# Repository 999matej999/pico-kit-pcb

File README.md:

# Pico Kit PCB #

## Files
* [Schematic](./rpi_pico_kit/RPi-Pico-Kit.pdf)
* [Gerber](./rpi_pico_kit/gerbers/)

## 3D Model

## Layout

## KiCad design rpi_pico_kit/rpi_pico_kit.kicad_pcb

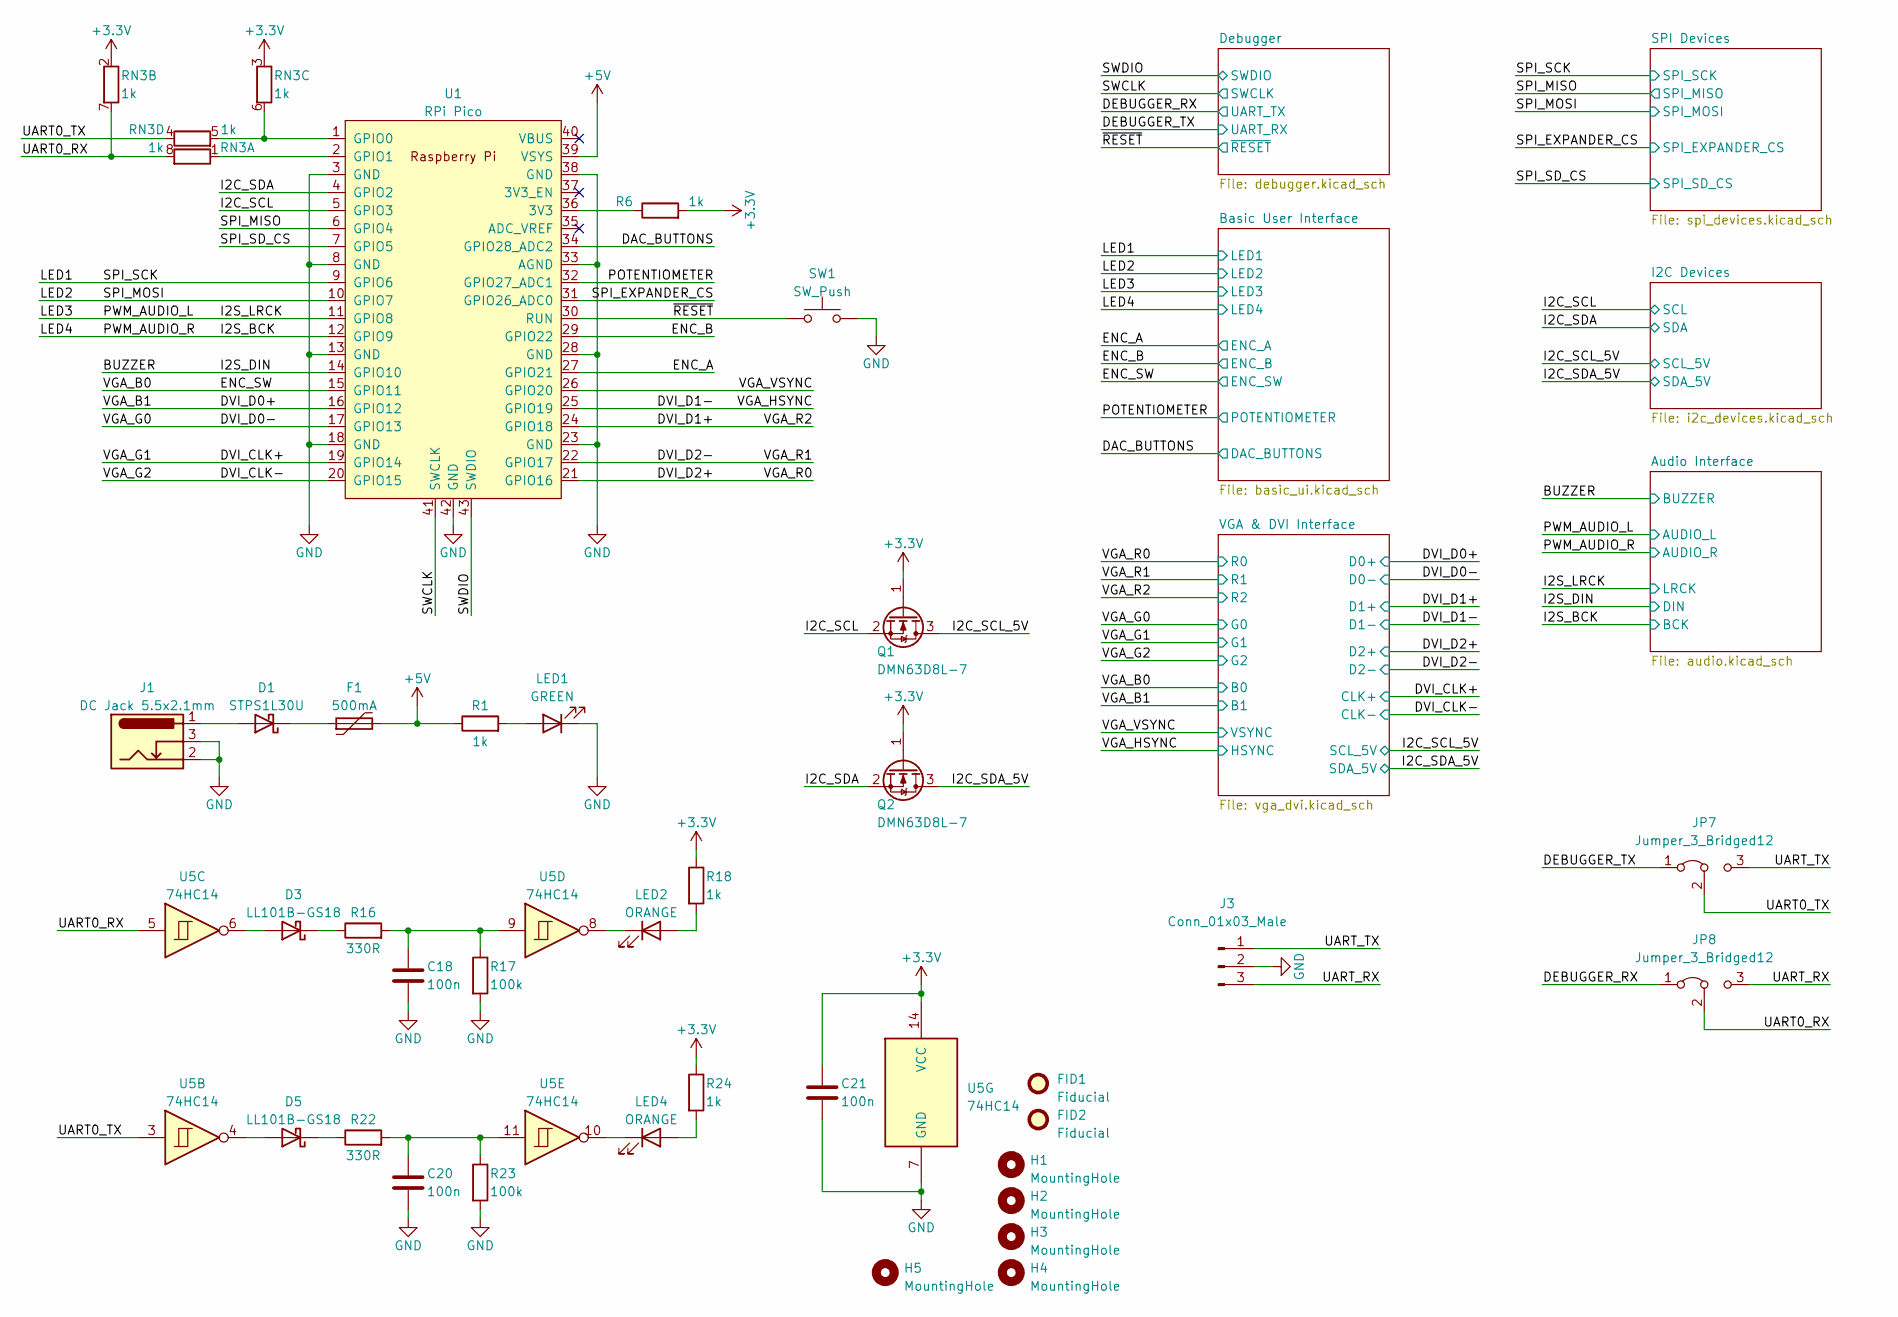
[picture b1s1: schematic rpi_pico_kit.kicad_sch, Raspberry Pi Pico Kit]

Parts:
C18, C20, C21: 100n; C_0603_1608Metric_Pad1.08x0.95mm_HandSolder; Manufacturer Part Number C0805C104M3RAC7800
D1: STPS1L30U; D_SMB; Manufacturer Part Number STPS1L30U
D3, D5: LL101B-GS18; D_MiniMELF; Manufacturer Part Number LL101B-GS18
F1: 500mA; Fuse_1206_3216Metric_Pad1.42x1.75mm_HandSolder; Manufacturer Part Number 0ZCJ0050FF2G
FID1, FID2: Fiducial; Fiducial_0.75mm_Mask1.5mm
H1, H2, H3, H4, H5: MountingHole; MountingHole_2.7mm_M2.5
J1: DC Jack 5.5x2.1mm; BarrelJack_GCT_DCJ200-10-A_Horizontal; Manufacturer Part Number 54-00129
J3: Conn_01x03_Male; PinHeader_1x03_P2.54mm_Vertical; Manufacturer Part Number PinHeader_1x03
JP7, JP8: Jumper_3_Bridged12; JumperTHT_3_P2.54mm_Bridged12; Manufacturer Part Number PinHeader_1x03
LED1: GREEN; LED_0805_2012Metric_Pad1.15x1.40mm_HandSolder; Manufacturer Part Number 150080VS75000
LED2, LED4: ORANGE; LED_0805_2012Metric_Pad1.15x1.40mm_HandSolder; Manufacturer Part Number LTST-C170KFKT
Q1, Q2: DMN63D8L-7; SOT-23; Manufacturer Part Number DMN63D8L-7
R1, R6, R18, R24: 1k; R_0603_1608Metric_Pad0.98x0.95mm_HandSolder; Manufacturer Part Number RC0805FR-071KL
R16, R22: 330R; R_0603_1608Metric_Pad0.98x0.95mm_HandSolder; Manufacturer Part Number RC0805FR-13330RL
R17, R23: 100k; R_0603_1608Metric_Pad0.98x0.95mm_HandSolder; Manufacturer Part Number RC0805FR-07100KL
RN3: 1k; R_Array_Convex_4x0603
SW1: SW_Push; SW_SPST_Omron_B3FS-100xP_12; Manufacturer Part Number TD-03XAT-A00-TR
U1: RPi Pico; RPi_Pico_THT_socket; Manufacturer Part Number SC0915
U5: 74HC14; SOIC-14_3.9x8.7mm_P1.27mm; Manufacturer Part Number 74HC14S14-13

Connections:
+3V3: C21.2, Q1.1 (G), Q2.1 (G), R6.2, R18.1, R24.1, RN3.2 (R2.1), RN3.3 (R3.1), U5.14 (VCC); also elsewhere on the board
+5V: F1.2, R1.1, U1.39 (VSYS); also elsewhere on the board
/BUZZER: U1.14 (GPIO10); also elsewhere on the board
/DAC_BUTTONS: U1.34 (GPIO28_ADC2); also elsewhere on the board
/DEBUGGER_RX: JP8.1 (A); also elsewhere on the board
/DEBUGGER_TX: JP7.1 (A); also elsewhere on the board
/DVI_CLK+: U1.19 (GPIO14); also elsewhere on the board
/DVI_CLK-: U1.20 (GPIO15); also elsewhere on the board
/DVI_D0+: U1.16 (GPIO12); also elsewhere on the board
/DVI_D0-: U1.17 (GPIO13); also elsewhere on the board
/DVI_D1+: U1.24 (GPIO18); also elsewhere on the board
/DVI_D1-: U1.25 (GPIO19); also elsewhere on the board
/DVI_D2+: U1.21 (GPIO16); also elsewhere on the board
/DVI_D2-: U1.22 (GPIO17); also elsewhere on the board
/ENC_A: U1.27 (GPIO21); also elsewhere on the board
/ENC_B: U1.29 (GPIO22); also elsewhere on the board
/ENC_SW: U1.15 (GPIO11); also elsewhere on the board
/I2C_SCL: Q1.2 (S), U1.5 (GPIO3); also elsewhere on the board
/I2C_SCL_5V: Q1.3 (D); also elsewhere on the board
/I2C_SDA: Q2.2 (S), U1.4 (GPIO2); also elsewhere on the board
/I2C_SDA_5V: Q2.3 (D); also elsewhere on the board
/I2S_BCK: U1.12 (GPIO9); also elsewhere on the board
/I2S_LRCK: U1.11 (GPIO8); also elsewhere on the board
/LED1: U1.9 (GPIO6); also elsewhere on the board
/LED2: U1.10 (GPIO7); also elsewhere on the board
/POTENTIOMETER: U1.32 (GPIO27_ADC1); also elsewhere on the board
/SPI_EXPANDER_CS: U1.31 (GPIO26_ADC0); also elsewhere on the board
/SPI_MISO: U1.6 (GPIO4); also elsewhere on the board
/SPI_SD_CS: U1.7 (GPIO5); also elsewhere on the board
/SWCLK: U1.41 (SWCLK); also elsewhere on the board
/SWDIO: U1.43 (SWDIO); also elsewhere on the board
/UART0_RX: JP8.2 (C), RN3.7 (R2.2), RN3.8 (R1.2), U5.5
/UART0_TX: JP7.2 (C), RN3.4 (R4.1), U5.3
/UART_RX: J3.3, JP8.3 (B)
/UART_TX: J3.1, JP7.3 (B)
/VGA_VSYNC: U1.26 (GPIO20); also elsewhere on the board
/~RESET: SW1.1, U1.30 (RUN); also elsewhere on the board
GND: C18.1, C20.1, C21.1, J1.2, J1.3, J3.2, LED1.1 (K), R17.2, R23.2, SW1.2, U1.3 (GND), U1.8 (GND), U1.13 (GND), U1.18 (GND), U1.23 (GND), U1.28 (GND), U1.33 (AGND), U1.38 (GND), U1.42 (GND), U5.7 (GND); also elsewhere on the board
unnamed: C18.2, R16.2, R17.1, U5.9
unnamed: C20.2, R22.2, R23.1, U5.11
unnamed: D1.2 (A), J1.1
unnamed: D1.1 (K), F1.1
unnamed: D3.2 (A), U5.6
unnamed: D3.1 (K), R16.1
unnamed: D5.2 (A), U5.4
unnamed: D5.1 (K), R22.1
unnamed: LED1.2 (A), R1.2
unnamed: LED2.2 (A), R18.2
unnamed: LED2.1 (K), U5.8
unnamed: LED4.2 (A), R24.2
unnamed: LED4.1 (K), U5.10
unnamed: RN3.1 (R1.1), U1.2 (GPIO1)
unnamed: RN3.5 (R4.2), RN3.6 (R3.2), U1.1 (GPIO0)
unnamed: R6.1, U1.36 (3V3)

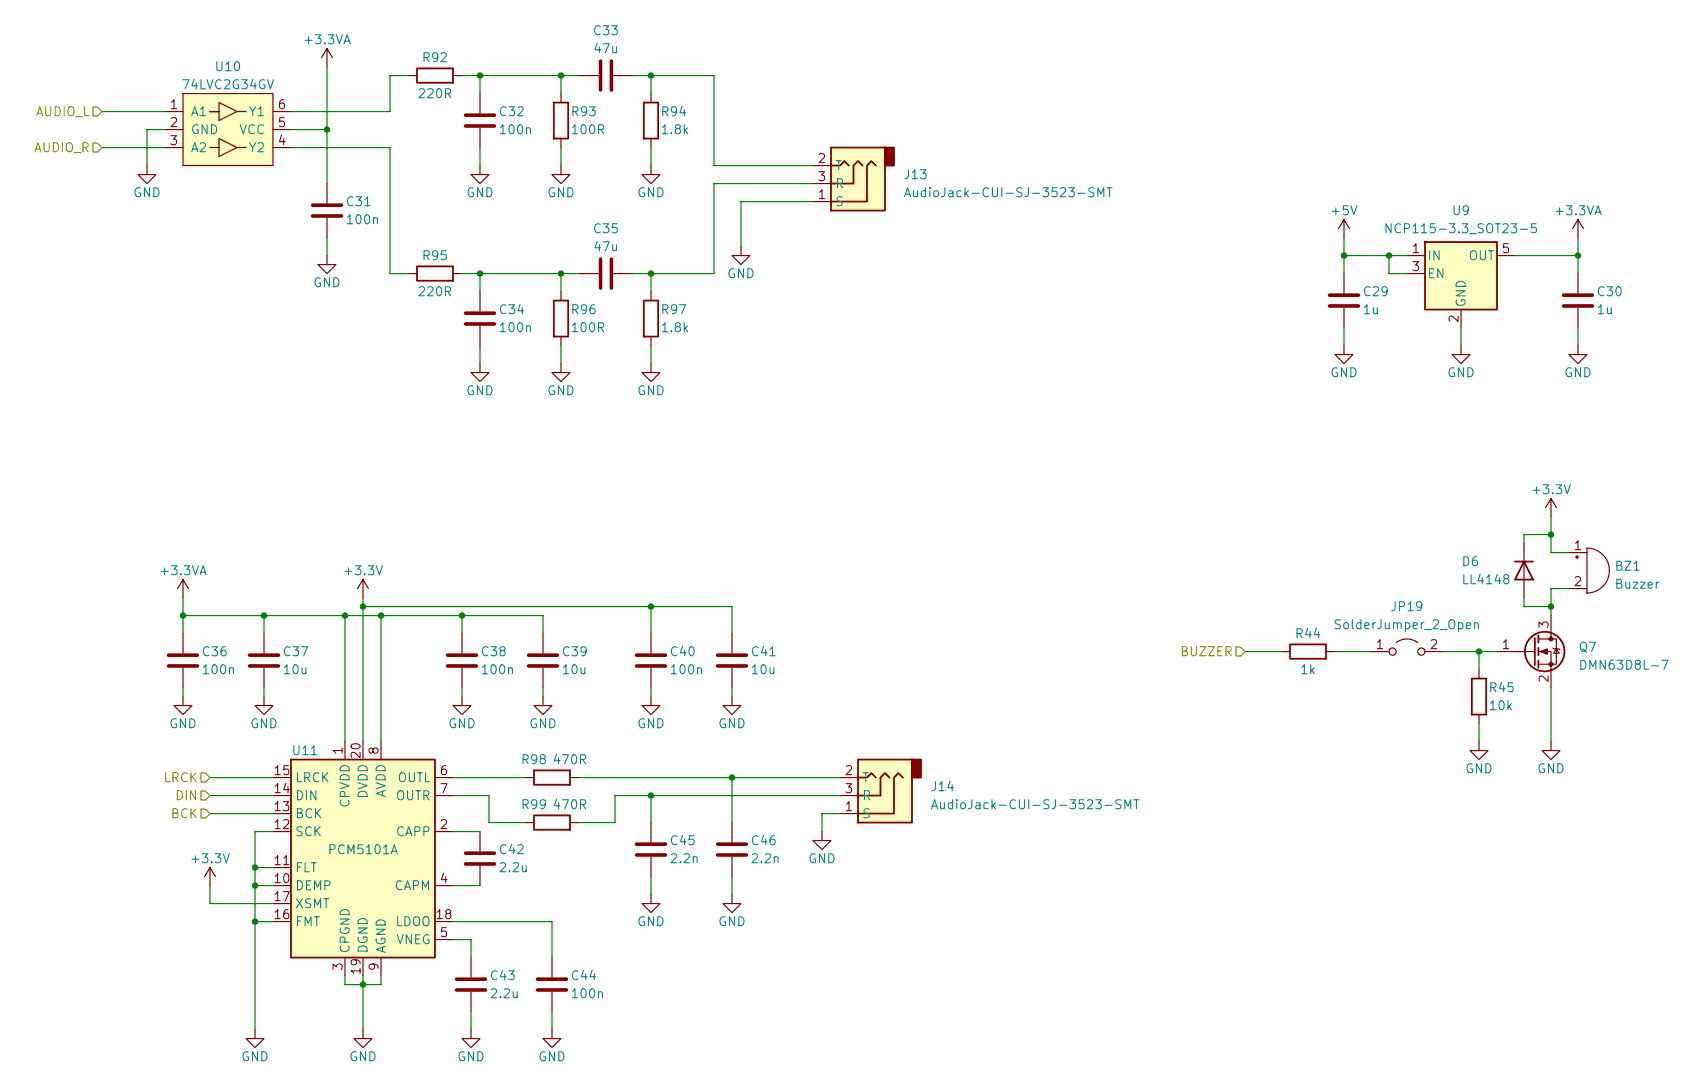
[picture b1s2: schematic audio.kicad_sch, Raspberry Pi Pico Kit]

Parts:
BZ1: Buzzer; Buzzer_12x9.5RM7.6; Manufacturer Part Number LA216001
C29, C30: 1u; C_0805_2012Metric_Pad1.18x1.45mm_HandSolder; Manufacturer Part Number C0805C105Z4VAC7800
C31, C32, C34, C36, C38, C40, C44: 100n; C_0603_1608Metric_Pad1.08x0.95mm_HandSolder; Manufacturer Part Number C0805C104M3RAC7800
C33, C35: 47u; C_0805_2012Metric_Pad1.18x1.45mm_HandSolder; Manufacturer Part Number CL21A476MRYNNNE
C37, C39, C41: 10u; C_0805_2012Metric_Pad1.18x1.45mm_HandSolder; Manufacturer Part Number CL21A106KOQNNNG
C42, C43: 2.2u; C_0805_2012Metric_Pad1.18x1.45mm_HandSolder; Manufacturer Part Number C0805C225Z4VAC7800
C45, C46: 2.2n; C_0603_1608Metric_Pad1.08x0.95mm_HandSolder; Manufacturer Part Number C0805C222K5RAC7800
D6: LL4148; D_MiniMELF; Manufacturer Part Number LL4148
J13, J14: AudioJack-CUI-SJ-3523-SMT; CUI_SJ-3523-audio-jack; Manufacturer Part Number SJ-3523-SMT-TR
JP19: SolderJumper_2_Open; JumperTHT_2_P2.54mm_Open; Manufacturer Part Number PinHeader_1x02
Q7: DMN63D8L-7; SOT-23; Manufacturer Part Number DMN63D8L-7
R44: 1k; R_0603_1608Metric_Pad0.98x0.95mm_HandSolder; Manufacturer Part Number RC0805FR-071KL
R45: 10k; R_0603_1608Metric_Pad0.98x0.95mm_HandSolder; Manufacturer Part Number RC0805FR-0710KL
R92, R95: 220R; R_0603_1608Metric_Pad0.98x0.95mm_HandSolder; Manufacturer Part Number RC0805FR-07220RL
R93, R96: 100R; R_0603_1608Metric_Pad0.98x0.95mm_HandSolder; Manufacturer Part Number RC0805FR-07100RL
R94, R97: 1.8k; R_0603_1608Metric_Pad0.98x0.95mm_HandSolder; Manufacturer Part Number RC0805FR-071K8L
R98, R99: 470R; R_0603_1608Metric_Pad0.98x0.95mm_HandSolder; Manufacturer Part Number RC0805FR-07470RL
U9: NCP115-3.3_SOT23-5; SOT-23-5; Manufacturer Part Number NCP115ASN330T2G
U10: 74LVC2G34GV; SC-74-6_1.5x2.9mm_P0.95mm; Manufacturer Part Number 74LVC2G34GV,125
U11: PCM5101A; TSSOP-20_4.4x6.5mm_P0.65mm

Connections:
+3.3VA: C30.2, C31.2, C36.2, C37.2, C38.2, C39.2, U9.5 (OUT), U10.5 (VCC), U11.1 (CPVDD), U11.8 (AVDD)
+3V3: BZ1.1 (-), C40.2, C41.2, D6.1 (K), U11.17 (XSMT), U11.20 (DVDD); also elsewhere on the board
+5V: C29.2, U9.1 (IN), U9.3 (EN); also elsewhere on the board
/BUZZER: R44.1, U11.14 (DIN); also elsewhere on the board
/I2S_BCK: U10.3 (A2), U11.13 (BCK); also elsewhere on the board
/I2S_LRCK: U10.1 (A1), U11.15 (LRCK); also elsewhere on the board
GND: C29.1, C30.1, C31.1, C32.1, C34.1, C36.1, C37.1, C38.1, C39.1, C40.1, C41.1, C43.1, C44.1, C45.1, C46.1, J13.1 (S), J14.1 (S), Q7.2 (S), R45.2, R93.2, R94.2, R96.2, R97.2, U9.2 (GND), U10.2 (GND), U11.3 (CPGND), U11.9 (AGND), U11.10 (DEMP), U11.11 (FLT), U11.12 (SCK), U11.16 (FMT), U11.19 (DGND); also elsewhere on the board
unnamed: BZ1.2 (+), D6.2 (A), Q7.3 (D)
unnamed: C32.2, C33.1, R92.2, R93.1
unnamed: C34.2, C35.1, R95.2, R96.1
unnamed: C35.2, J13.3 (R), R97.1
unnamed: C33.2, J13.2 (T), R94.1
unnamed: C45.2, J14.3 (R), R99.2
unnamed: C46.2, J14.2 (T), R98.2
unnamed: JP19.1 (A), R44.2
unnamed: JP19.2 (B), Q7.1 (G), R45.1
unnamed: R92.1, U10.6 (Y1)
unnamed: R95.1, U10.4 (Y2)
unnamed: C42.1, U11.4 (CAPM)
unnamed: C42.2, U11.2 (CAPP)
unnamed: C44.2, U11.18 (LDOO)
unnamed: R98.1, U11.6 (OUTL)
unnamed: R99.1, U11.7 (OUTR)
unnamed: C43.2, U11.5 (VNEG)

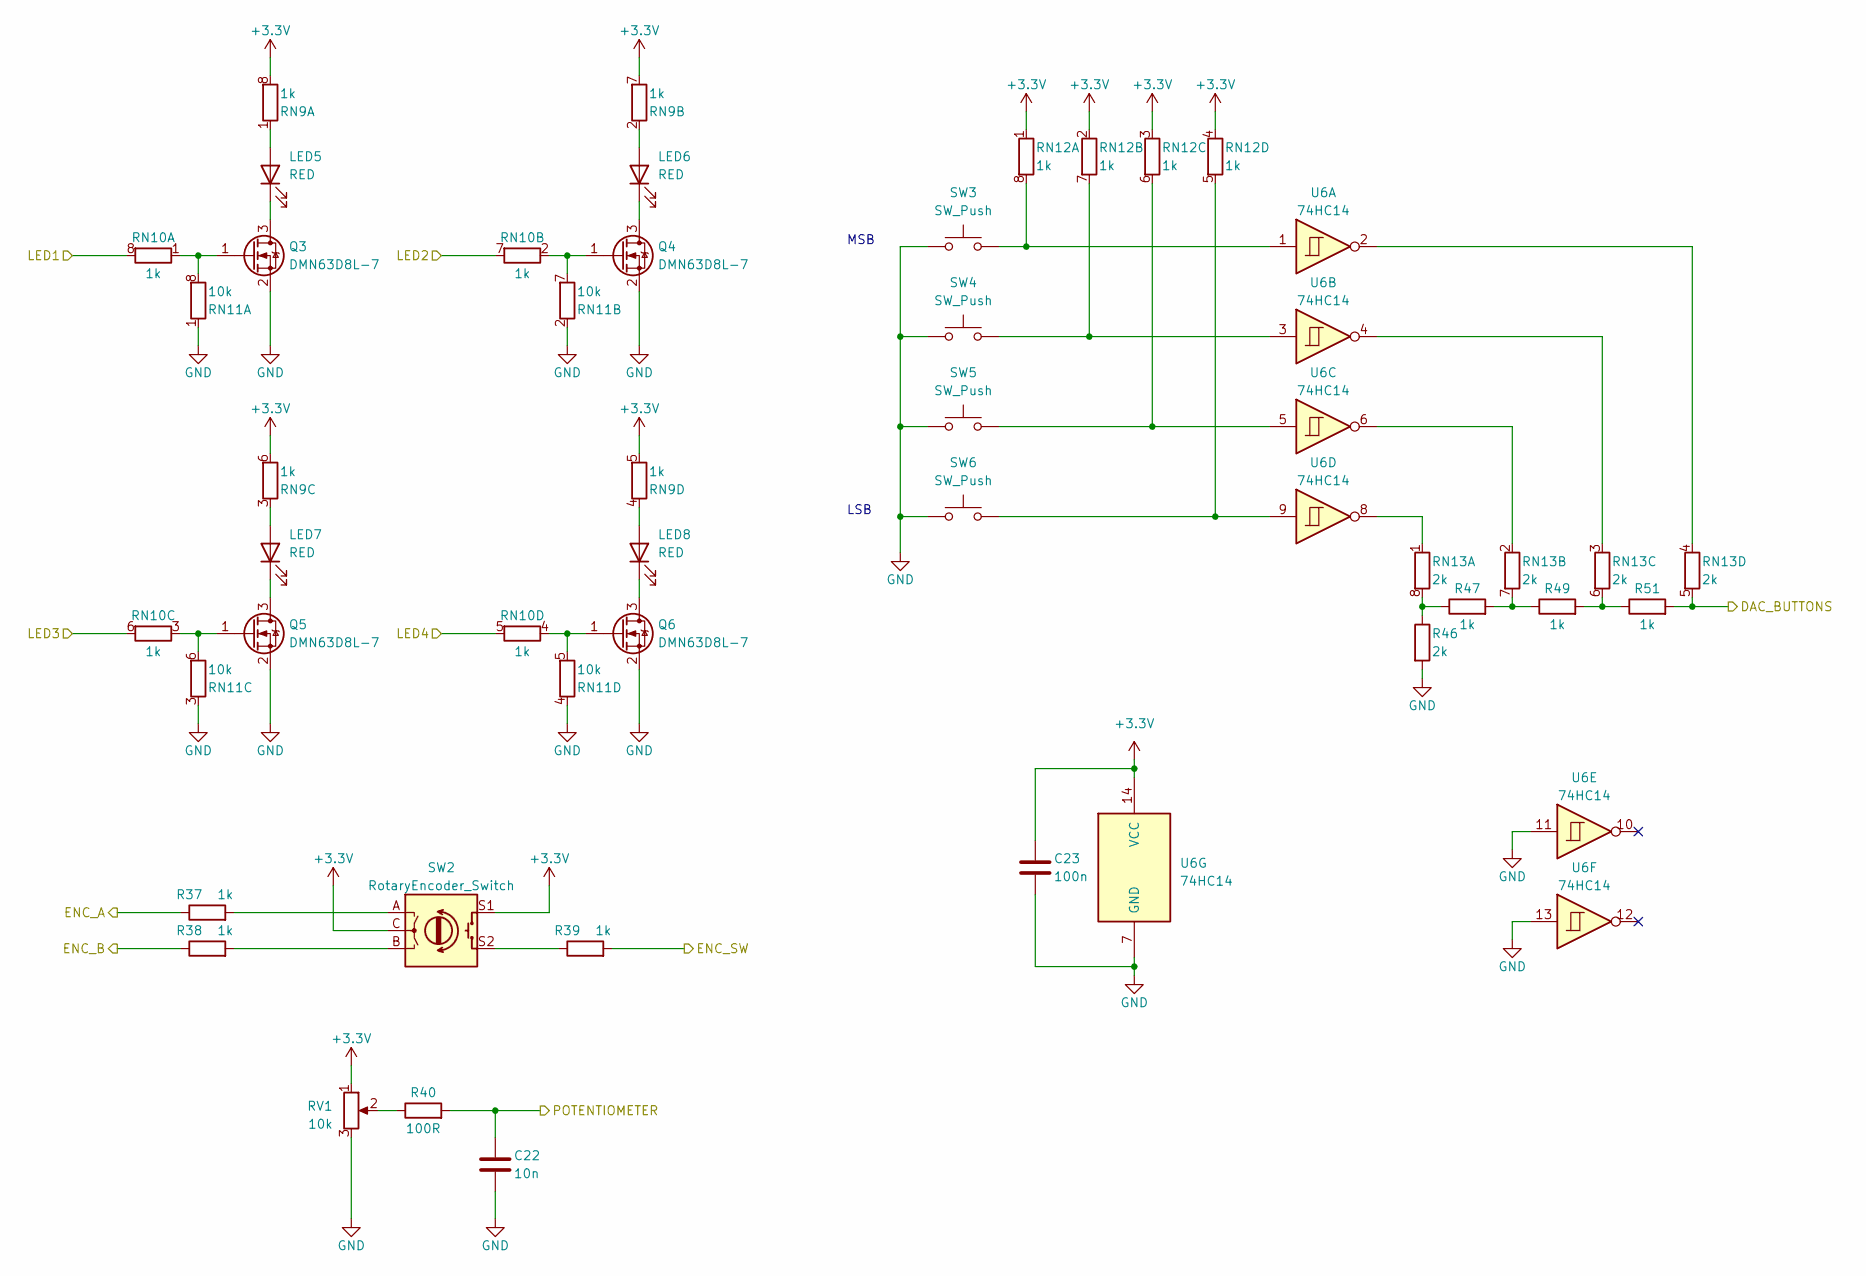
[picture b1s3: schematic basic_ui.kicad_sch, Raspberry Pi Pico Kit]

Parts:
C22: 10n; C_0603_1608Metric_Pad1.08x0.95mm_HandSolder; Manufacturer Part Number C0805C103K5RAC7210
C23: 100n; C_0603_1608Metric_Pad1.08x0.95mm_HandSolder; Manufacturer Part Number C0805C104M3RAC7800
LED5, LED6, LED7, LED8: RED; LED_0805_2012Metric_Pad1.15x1.40mm_HandSolder; Manufacturer Part Number 150080SS75000
Q3, Q4, Q5, Q6: DMN63D8L-7; SOT-23; Manufacturer Part Number DMN63D8L-7
R37, R38, R39, R47, R49, R51: 1k; R_0603_1608Metric_Pad0.98x0.95mm_HandSolder; Manufacturer Part Number RC0805FR-071KL
R40: 100R; R_0603_1608Metric_Pad0.98x0.95mm_HandSolder; Manufacturer Part Number RC0805FR-07100RL
R46: 2k; R_0603_1608Metric_Pad0.98x0.95mm_HandSolder; Manufacturer Part Number RC0805FR-072KL
RN9, RN10, RN12: 1k; R_Array_Convex_4x0603
RN11: 10k; R_Array_Convex_4x0603
RN13: 2k; R_Array_Convex_4x0603
RV1: 10k; Potentiometer_Bourns_PTV09A-1_Single_Vertical; Manufacturer Part Number PT01-B125D-B103
SW2: RotaryEncoder_Switch; RotaryEncoder_Alps_EC11E-Switch_Vertical_H20mm; Manufacturer Part Number EN11-HSM1BF20
SW3, SW4, SW5, SW6: SW_Push; SW_SPST_Omron_B3FS-100xP_12; Manufacturer Part Number TD-03XAT-A00-TR
U6: 74HC14; SOIC-14_3.9x8.7mm_P1.27mm; Manufacturer Part Number 74HC14S14-13

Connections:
+3V3: C23.2, RN9.5 (R4.2), RN9.6 (R3.2), RN9.7 (R2.2), RN9.8 (R1.2), RN12.1 (R1.1), RN12.2 (R2.1), RN12.3 (R3.1), RN12.4 (R4.1), RV1.1, SW2.C, SW2.S1, U6.14 (VCC); also elsewhere on the board
/DAC_BUTTONS: R51.2, RN13.5 (R4.2); also elsewhere on the board
/ENC_A: R37.1; also elsewhere on the board
/ENC_B: R38.1; also elsewhere on the board
/ENC_SW: R39.2; also elsewhere on the board
/I2S_BCK: RN10.5 (R4.2); also elsewhere on the board
/I2S_LRCK: RN10.6 (R3.2); also elsewhere on the board
/LED1: RN10.8 (R1.2); also elsewhere on the board
/LED2: RN10.7 (R2.2); also elsewhere on the board
/POTENTIOMETER: C22.1, R40.2; also elsewhere on the board
GND: C22.2, C23.1, Q3.2 (S), Q4.2 (S), Q5.2 (S), Q6.2 (S), R46.2, RN11.1 (R1.1), RN11.2 (R2.1), RN11.3 (R3.1), RN11.4 (R4.1), RV1.3, SW3.2, SW4.2, SW5.2, SW6.2, U6.7 (GND), U6.11, U6.13; also elsewhere on the board
unnamed: LED5.2 (A), RN9.1 (R1.1)
unnamed: LED5.1 (K), Q3.3 (D)
unnamed: LED6.2 (A), RN9.2 (R2.1)
unnamed: LED6.1 (K), Q4.3 (D)
unnamed: LED7.2 (A), RN9.3 (R3.1)
unnamed: LED7.1 (K), Q5.3 (D)
unnamed: LED8.2 (A), RN9.4 (R4.1)
unnamed: LED8.1 (K), Q6.3 (D)
unnamed: Q3.1 (G), RN10.1 (R1.1), RN11.8 (R1.2)
unnamed: Q4.1 (G), RN10.2 (R2.1), RN11.7 (R2.2)
unnamed: Q5.1 (G), RN10.3 (R3.1), RN11.6 (R3.2)
unnamed: Q6.1 (G), RN10.4 (R4.1), RN11.5 (R4.2)
unnamed: R37.2, SW2.A
unnamed: R38.2, SW2.B
unnamed: R39.1, SW2.S2
unnamed: R40.1, RV1.2
unnamed: RN12.8 (R1.2), SW3.1, U6.1
unnamed: RN12.7 (R2.2), SW4.1, U6.3
unnamed: RN12.6 (R3.2), SW5.1, U6.5
unnamed: RN12.5 (R4.2), SW6.1, U6.9
unnamed: RN13.1 (R1.1), U6.8
unnamed: R46.1, R47.1, RN13.8 (R1.2)
unnamed: RN13.2 (R2.1), U6.6
unnamed: R47.2, R49.1, RN13.7 (R2.2)
unnamed: RN13.3 (R3.1), U6.4
unnamed: R49.2, R51.1, RN13.6 (R3.2)
unnamed: RN13.4 (R4.1), U6.2

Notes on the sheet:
LSB
MSB

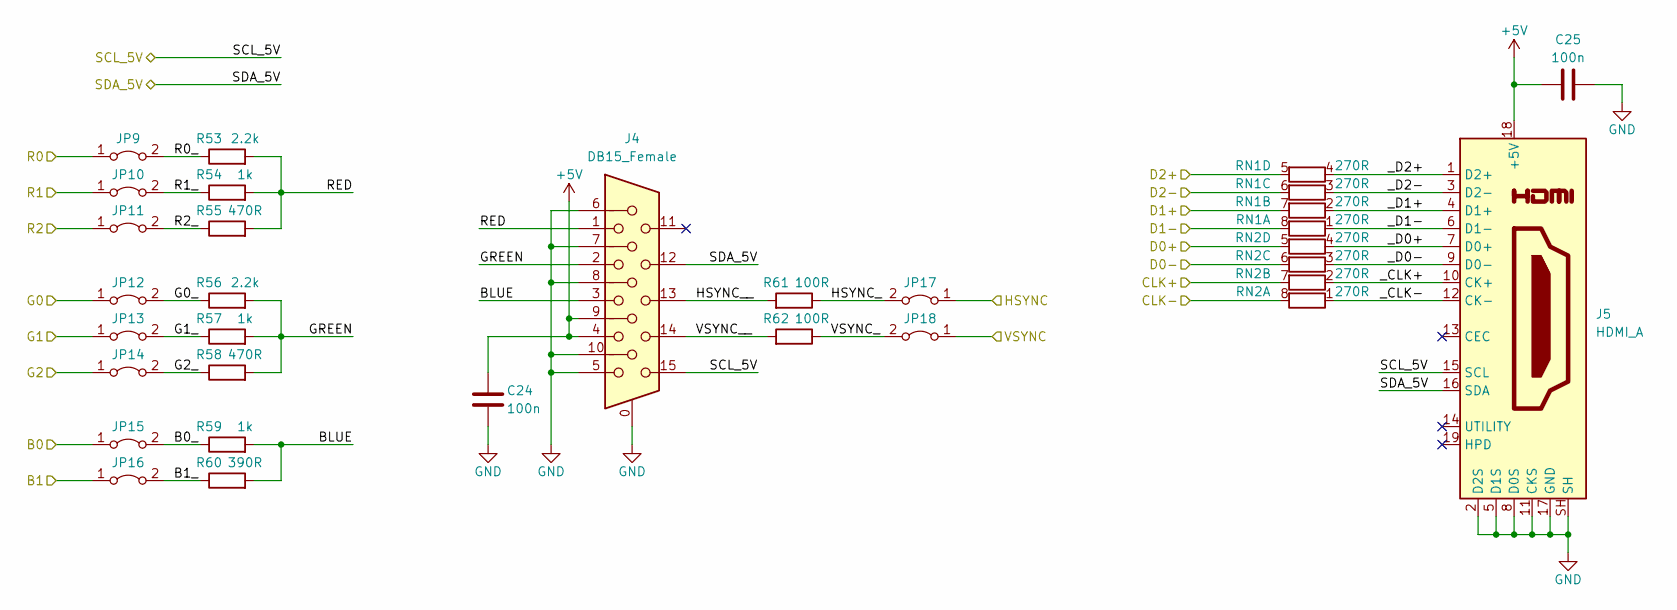
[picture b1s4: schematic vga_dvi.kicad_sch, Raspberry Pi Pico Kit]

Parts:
C24, C25: 100n; C_0603_1608Metric_Pad1.08x0.95mm_HandSolder; Manufacturer Part Number C0805C104M3RAC7800
J4: DB15_Female; DSUB-15-HD_Female_Horizontal_P2.29x1.98mm_EdgePinOffset3.03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
J5: HDMI_A; STEWART_SS-53000-001; Manufacturer Part Number SS-53000-001
JP9, JP10, JP11, JP12, JP13, JP14, JP15, JP16, JP17, JP18: Jumper_2_Bridged; JumperTHT_2_P2.54mm_Bridged; Manufacturer Part Number PinHeader_1x02
R53, R56: 2.2k; R_0603_1608Metric_Pad0.98x0.95mm_HandSolder; Manufacturer Part Number RC0805FR-072K2L
R54, R57, R59: 1k; R_0603_1608Metric_Pad0.98x0.95mm_HandSolder; Manufacturer Part Number RC0805FR-071KL
R55, R58: 470R; R_0603_1608Metric_Pad0.98x0.95mm_HandSolder; Manufacturer Part Number RC0805FR-07470RL
R60: 390R; R_0603_1608Metric_Pad0.98x0.95mm_HandSolder; Manufacturer Part Number RC0805FR-07390RL
R61, R62: 100R; R_0603_1608Metric_Pad0.98x0.95mm_HandSolder; Manufacturer Part Number RC0805FR-07100RL
RN1, RN2: 270R; R_Array_Convex_4x0603

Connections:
+5V: C24.2, C25.1, J4.4, J4.9, J5.18 (+5V); also elsewhere on the board
/DVI_CLK+: JP13.1 (A), RN2.7 (R2.2); also elsewhere on the board
/DVI_CLK-: JP14.1 (A), RN2.8 (R1.2); also elsewhere on the board
/DVI_D0+: JP16.1 (A), RN2.5 (R4.2); also elsewhere on the board
/DVI_D0-: JP12.1 (A), RN2.6 (R3.2); also elsewhere on the board
/DVI_D1+: JP11.1 (A), RN1.7 (R2.2); also elsewhere on the board
/DVI_D1-: JP17.1 (A), RN1.8 (R1.2); also elsewhere on the board
/DVI_D2+: JP9.1 (A), RN1.5 (R4.2); also elsewhere on the board
/DVI_D2-: JP10.1 (A), RN1.6 (R3.2); also elsewhere on the board
/ENC_SW: JP15.1 (A); also elsewhere on the board
/I2C_SCL_5V: J4.15, J5.15 (SCL); also elsewhere on the board
/I2C_SDA_5V: J4.12, J5.16 (SDA); also elsewhere on the board
/VGA & DVI Interface/B0_: JP15.2 (B), R59.1
/VGA & DVI Interface/B1_: JP16.2 (B), R60.1
/VGA & DVI Interface/BLUE: J4.3, R59.2, R60.2
/VGA & DVI Interface/G0_: JP12.2 (B), R56.1
/VGA & DVI Interface/G1_: JP13.2 (B), R57.1
/VGA & DVI Interface/G2_: JP14.2 (B), R58.1
/VGA & DVI Interface/GREEN: J4.2, R56.2, R57.2, R58.2
/VGA & DVI Interface/HSYNC_: JP17.2 (B), R61.1
/VGA & DVI Interface/HSYNC__: J4.13, R61.2
/VGA & DVI Interface/R0_: JP9.2 (B), R53.1
/VGA & DVI Interface/R1_: JP10.2 (B), R54.1
/VGA & DVI Interface/R2_: JP11.2 (B), R55.1
/VGA & DVI Interface/RED: J4.1, R53.2, R54.2, R55.2
/VGA & DVI Interface/VSYNC_: JP18.2 (B), R62.1
/VGA & DVI Interface/VSYNC__: J4.14, R62.2
/VGA & DVI Interface/_CLK+: J5.10 (CK+), RN2.2 (R2.1)
/VGA & DVI Interface/_CLK-: J5.12 (CK-), RN2.1 (R1.1)
/VGA & DVI Interface/_D0+: J5.7 (D0+), RN2.4 (R4.1)
/VGA & DVI Interface/_D0-: J5.9 (D0-), RN2.3 (R3.1)
/VGA & DVI Interface/_D1+: J5.4 (D1+), RN1.2 (R2.1)
/VGA & DVI Interface/_D1-: J5.6 (D1-), RN1.1 (R1.1)
/VGA & DVI Interface/_D2+: J5.1 (D2+), RN1.4 (R4.1)
/VGA & DVI Interface/_D2-: J5.3 (D2-), RN1.3 (R3.1)
/VGA_VSYNC: JP18.1 (A); also elsewhere on the board
GND: C24.1, C25.2, J4.0, J4.5, J4.6, J4.7, J4.8, J4.10, J5.2 (D2S), J5.5 (D1S), J5.8 (D0S), J5.11 (CKS), J5.17 (GND), J5.SH; also elsewhere on the board

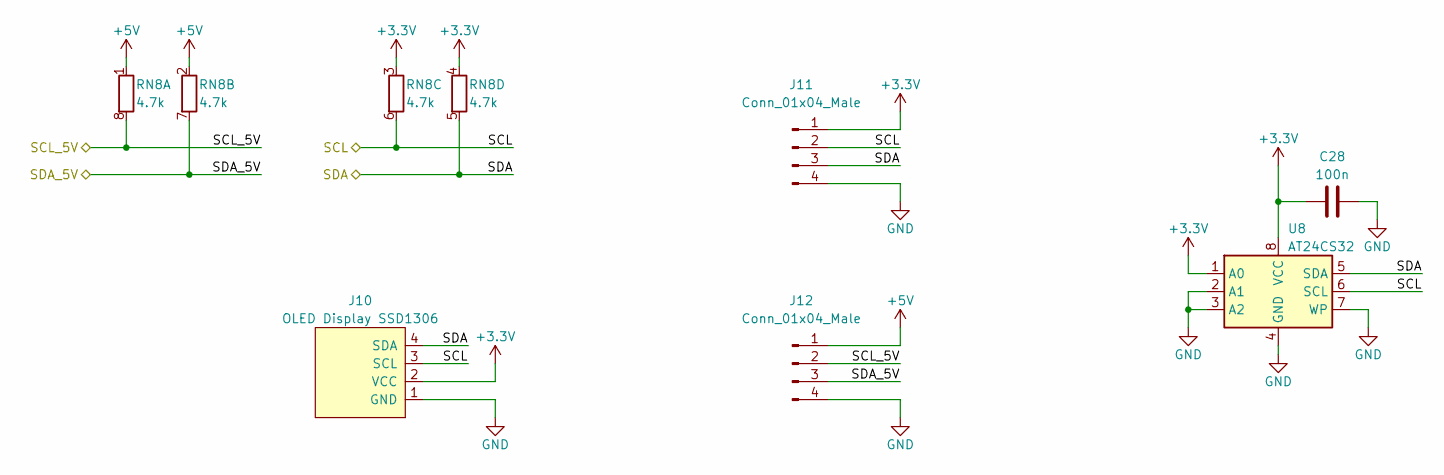
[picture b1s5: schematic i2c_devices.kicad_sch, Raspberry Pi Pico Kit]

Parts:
C28: 100n; C_0603_1608Metric_Pad1.08x0.95mm_HandSolder; Manufacturer Part Number C0805C104M3RAC7800
J10: OLED Display SSD1306; 128x64OLED; Manufacturer Part Number LA141008DI
J11, J12: Conn_01x04_Male; PinHeader_1x04_P2.54mm_Vertical; Manufacturer Part Number PinHeader_1x04
RN8: 4.7k; R_Array_Convex_4x0603
U8: AT24CS32; SOIC-8_3.9x4.9mm_P1.27mm; Manufacturer Part Number CAT24C32WI-GT3

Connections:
+3V3: C28.1, J10.2 (VCC), J11.1, RN8.3 (R3.1), RN8.4 (R4.1), U8.1 (A0), U8.8 (VCC); also elsewhere on the board
+5V: J12.1, RN8.1 (R1.1), RN8.2 (R2.1); also elsewhere on the board
/I2C_SCL: J10.3 (SCL), J11.2, RN8.6 (R3.2), U8.6 (SCL); also elsewhere on the board
/I2C_SCL_5V: J12.2, RN8.8 (R1.2); also elsewhere on the board
/I2C_SDA: J10.4 (SDA), J11.3, RN8.5 (R4.2), U8.5 (SDA); also elsewhere on the board
/I2C_SDA_5V: J12.3, RN8.7 (R2.2); also elsewhere on the board
GND: C28.2, J10.1 (GND), J11.4, J12.4, U8.2 (A1), U8.3 (A2), U8.4 (GND), U8.7 (WP); also elsewhere on the board

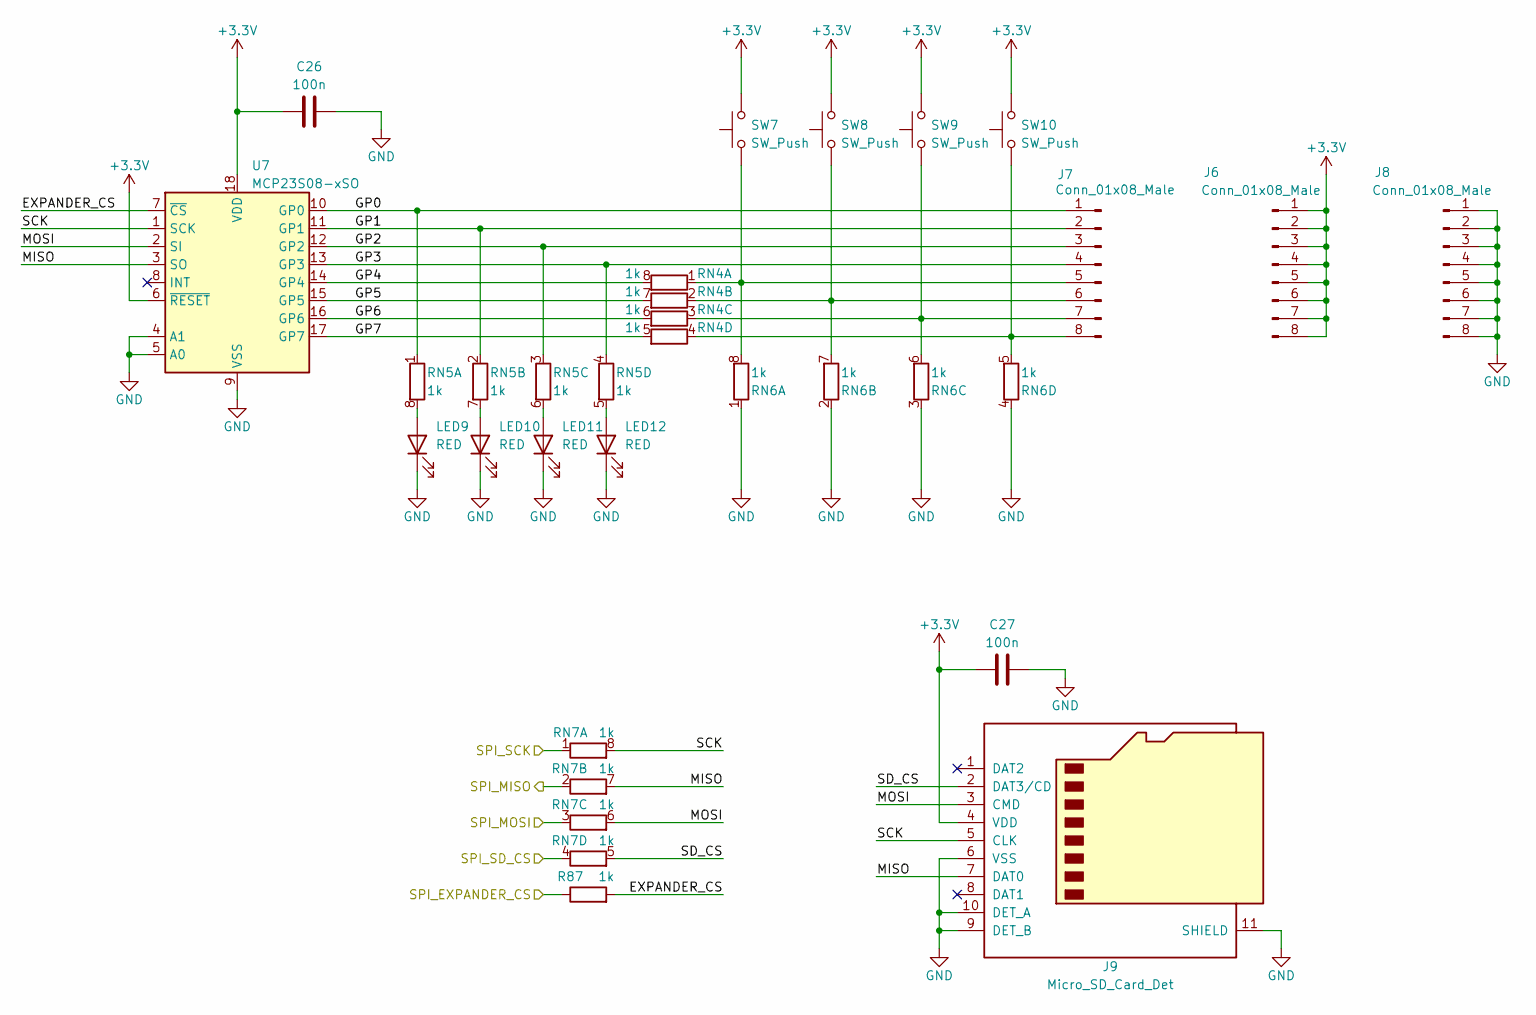
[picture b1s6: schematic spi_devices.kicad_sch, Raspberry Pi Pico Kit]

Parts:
C26, C27: 100n; C_0603_1608Metric_Pad1.08x0.95mm_HandSolder; Manufacturer Part Number C0805C104M3RAC7800
J6, J7, J8: Conn_01x08_Male; PinHeader_1x08_P2.54mm_Vertical; Manufacturer Part Number PinHeader_1x08
J9: Micro_SD_Card_Det; microSD_HC_Molex_104031-0811; Manufacturer Part Number 1040310811
LED9, LED10, LED11, LED12: RED; LED_0805_2012Metric_Pad1.15x1.40mm_HandSolder; Manufacturer Part Number 150080SS75000
R87: 1k; R_0603_1608Metric_Pad0.98x0.95mm_HandSolder; Manufacturer Part Number RC0805FR-071KL
RN4, RN5, RN6, RN7: 1k; R_Array_Convex_4x0603
SW7, SW8, SW9, SW10: SW_Push; SW_SPST_Omron_B3FS-100xP_12; Manufacturer Part Number TD-03XAT-A00-TR
U7: MCP23S08-xSO; SOIC-18W_7.5x11.6mm_P1.27mm; Manufacturer Part Number MCP23S08-E/SO

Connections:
+3V3: C26.1, C27.1, J6.1, J6.2, J6.3, J6.4, J6.5, J6.6, J6.7, J6.8, J9.4 (VDD), SW7.2, SW8.2, SW9.2, SW10.2, U7.6 (~RESET), U7.18 (VDD); also elsewhere on the board
/LED1: RN7.1 (R1.1); also elsewhere on the board
/LED2: RN7.3 (R3.1); also elsewhere on the board
/SPI Devices/EXPANDER_CS: R87.2, U7.7 (~CS)
/SPI Devices/GP0: J7.1, RN5.1 (R1.1), U7.10 (GP0)
/SPI Devices/GP1: J7.2, RN5.2 (R2.1), U7.11 (GP1)
/SPI Devices/GP2: J7.3, RN5.3 (R3.1), U7.12 (GP2)
/SPI Devices/GP3: J7.4, RN5.4 (R4.1), U7.13 (GP3)
/SPI Devices/GP4: RN4.8 (R1.2), U7.14 (GP4)
/SPI Devices/GP5: RN4.7 (R2.2), U7.15 (GP5)
/SPI Devices/GP6: RN4.6 (R3.2), U7.16 (GP6)
/SPI Devices/GP7: RN4.5 (R4.2), U7.17 (GP7)
/SPI Devices/MISO: J9.7 (DAT0), RN7.7 (R2.2), U7.3 (SO)
/SPI Devices/MOSI: J9.3 (CMD), RN7.6 (R3.2), U7.2 (SI)
/SPI Devices/SCK: J9.5 (CLK), RN7.8 (R1.2), U7.1 (SCK)
/SPI Devices/SD_CS: J9.2 (DAT3/CD), RN7.5 (R4.2)
/SPI_EXPANDER_CS: R87.1; also elsewhere on the board
/SPI_MISO: RN7.2 (R2.1); also elsewhere on the board
/SPI_SD_CS: RN7.4 (R4.1); also elsewhere on the board
GND: C26.2, C27.2, J8.1, J8.2, J8.3, J8.4, J8.5, J8.6, J8.7, J8.8, J9.6 (VSS), J9.9 (DET_B), J9.10 (DET_A), J9.11 (SHIELD), LED9.1 (K), LED10.1 (K), LED11.1 (K), LED12.1 (K), RN6.1 (R1.1), RN6.2 (R2.1), RN6.3 (R3.1), RN6.4 (R4.1), U7.4 (A1), U7.5 (A0), U7.9 (VSS); also elsewhere on the board
unnamed: J7.5, RN4.1 (R1.1), RN6.8 (R1.2), SW7.1
unnamed: J7.6, RN4.2 (R2.1), RN6.7 (R2.2), SW8.1
unnamed: J7.7, RN4.3 (R3.1), RN6.6 (R3.2), SW9.1
unnamed: J7.8, RN4.4 (R4.1), RN6.5 (R4.2), SW10.1
unnamed: LED9.2 (A), RN5.8 (R1.2)
unnamed: LED10.2 (A), RN5.7 (R2.2)
unnamed: LED11.2 (A), RN5.6 (R3.2)
unnamed: LED12.2 (A), RN5.5 (R4.2)
